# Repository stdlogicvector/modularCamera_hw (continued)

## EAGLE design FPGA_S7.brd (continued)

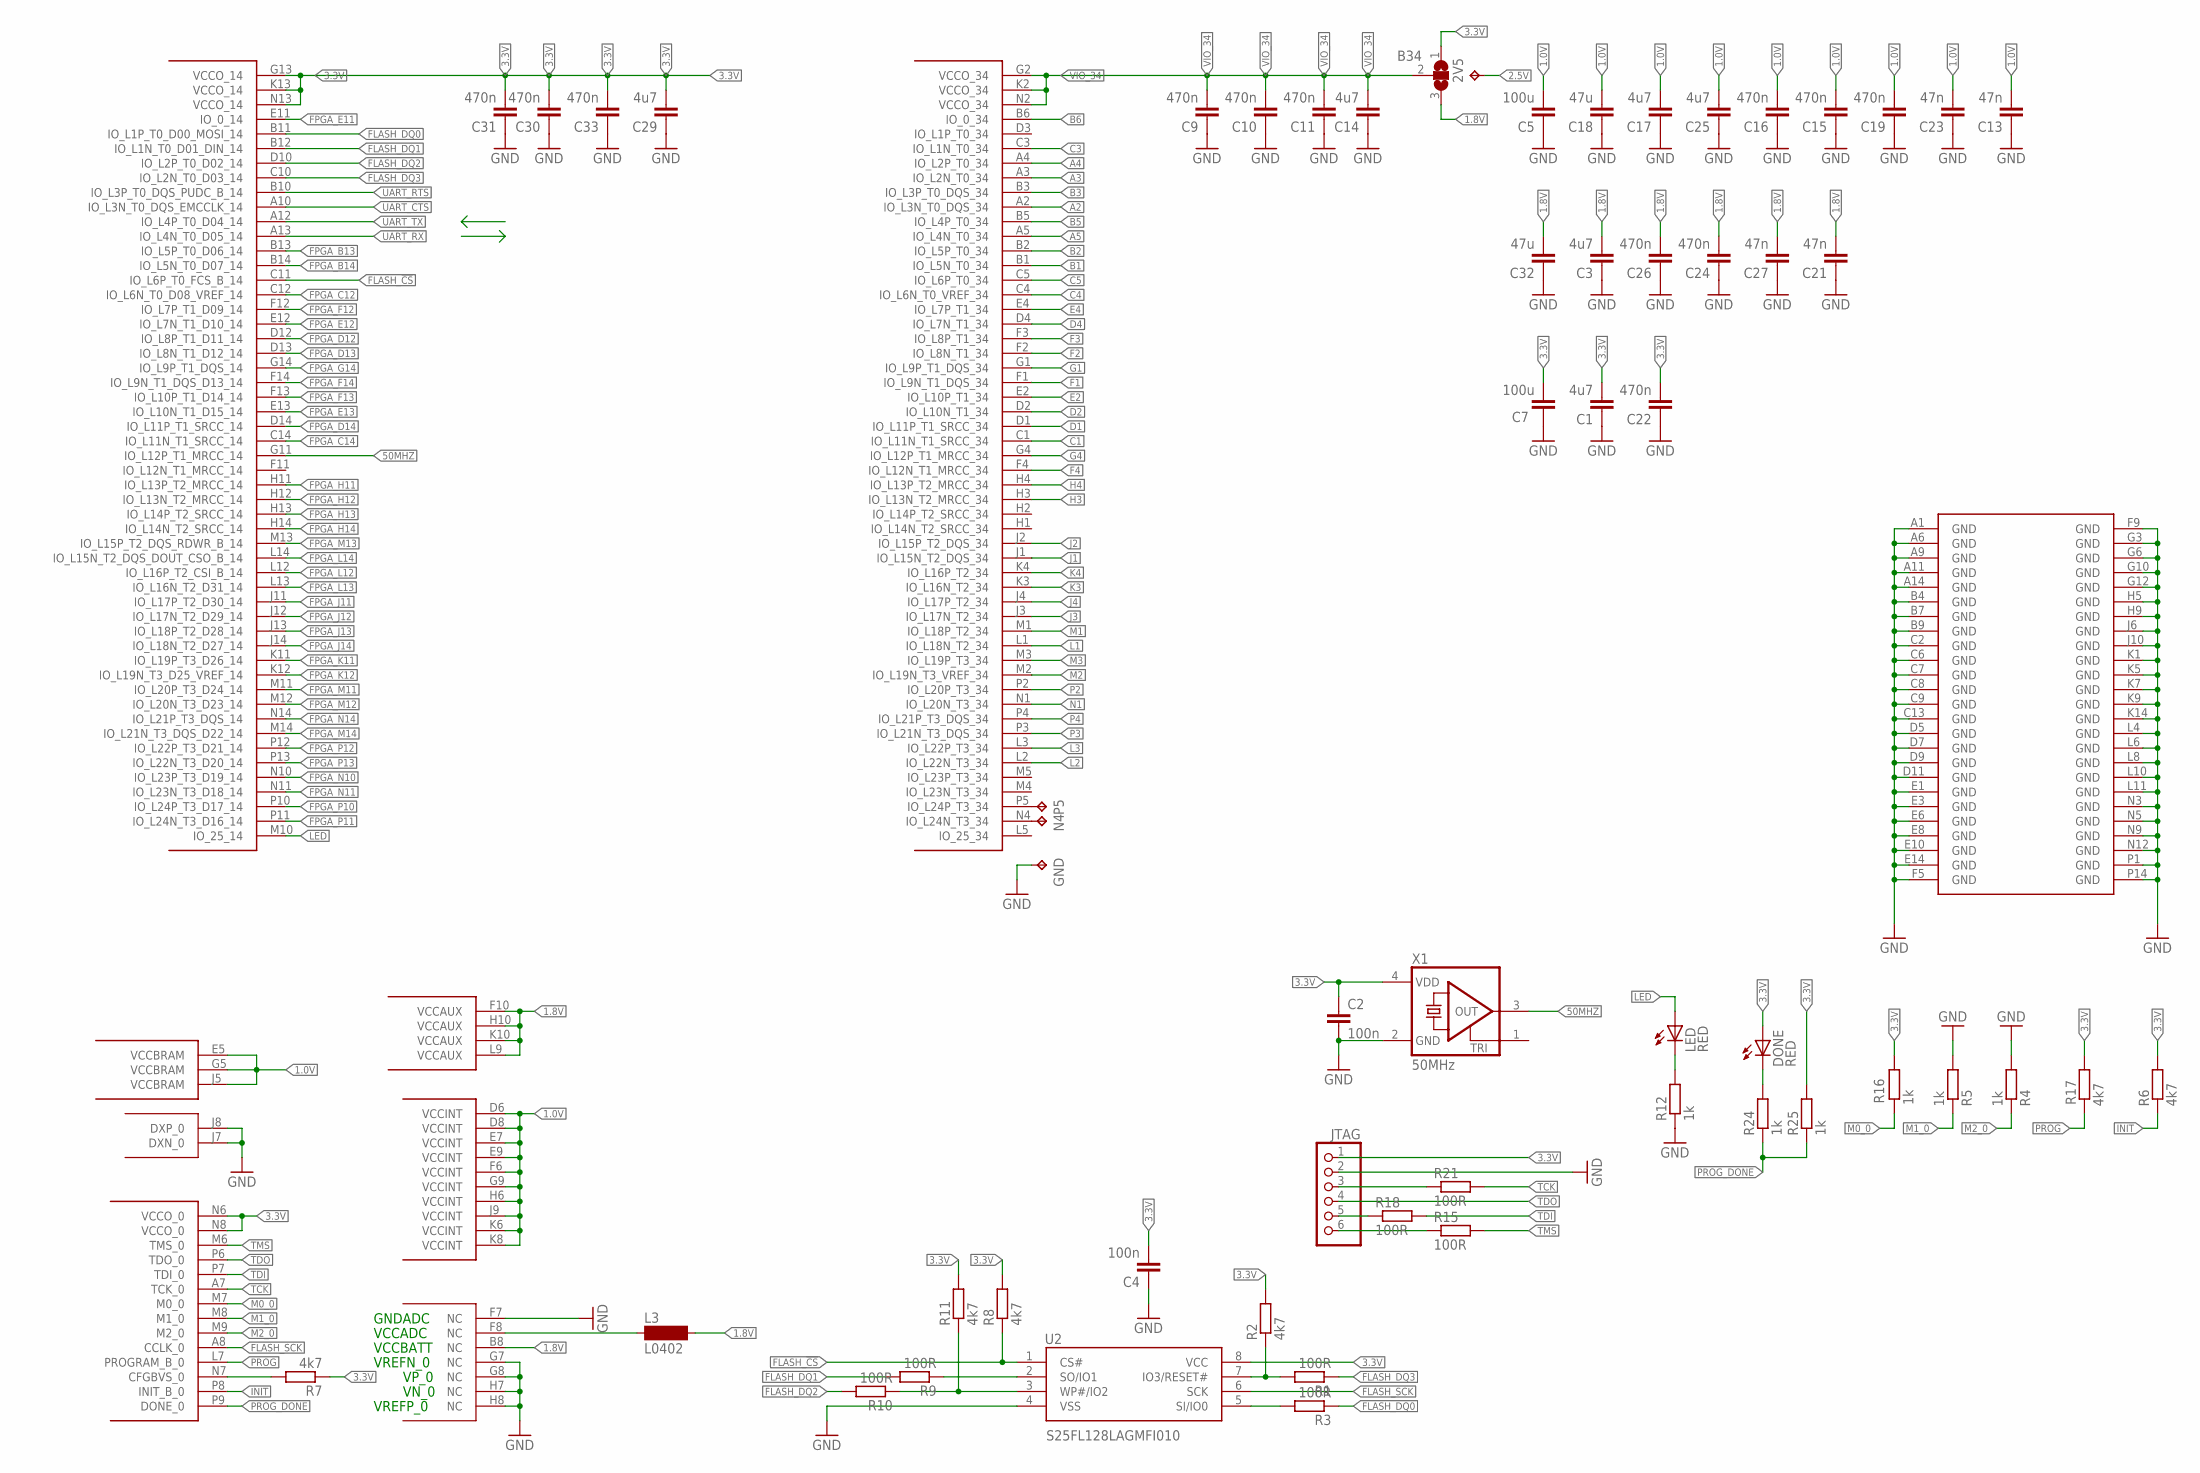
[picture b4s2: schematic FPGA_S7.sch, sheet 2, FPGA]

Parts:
2V5: TPTP12SQ; TP12SQ
B34: SJ2W; SJ_2
C1, C3, C14, C17, C25, C29: 4u7; C0603; LCSC C19666
C2, C4: 100n; C0402; LCSC C1525
C5, C7: 100u; C1206; DIGIKEY 490-GRM31CD80J107MEA8LCT-ND
C9, C10, C11, C15, C16, C19, C22, C24, C26, C30, C31, C33: 470n; C0402; LCSC C162159
C13, C21, C23, C27: 47n; C0402; LCSC C327054
C18, C32: 47u; C0805; LCSC C77072
DONE: RED; CHIP-LED0603; LCSC C7493803
GND: TPTP15R; TP15R
JTAG: PINHD-1X6_2.00; 1X06M
L3: L0402; C0402; LCSC C88970
LED: RED; CHIP-LED0603; LCSC C7493803
N4: TPTP15R; TP15R
P5: TPTP15R; TP15R
R1, R3, R9, R10, R15, R18, R21: 100R; R0402; LCSC C25076
R2, R6, R7, R8, R11, R17: 4k7; R0402; LCSC C25900
R4: 1k; R0402; LCSC C106235
R5, R12, R16, R24, R25: 1k; R0402; LCSC C11702
U1: XC7S15-2FTGB196I; BGA196C100P14X14_1500X1500X155; DIGIKEY 122-2233-ND
U2: S25FL128LAGMFI010; SOIC127P800X216-8N; MPN S25FL128LAGMFI010; DIGIKEY 448-S25FL128LAGMFI010-ND
X1: 50MHz; ASE; MPN_ ASE-50.000MHZ-E-T; FARNELL 2467898

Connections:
1.0V: C5.1, C13.2, C15.2, C16.2, C17.2, C18.1, C19.2, C23.2, C25.2, U1.D6 (VCCINT), U1.D8 (VCCINT), U1.E5 (VCCBRAM), U1.E7 (VCCINT), U1.E9 (VCCINT), U1.F6 (VCCINT), U1.G5 (VCCBRAM), U1.G9 (VCCINT), U1.H6 (VCCINT), U1.J5 (VCCBRAM), U1.J9 (VCCINT), U1.K6 (VCCINT), U1.K8 (VCCINT); also elsewhere on the board
1.8V: B34.3, C3.2, C21.2, C24.2, C26.2, C27.2, C32.2, L3.2, U1.B8 (NC), U1.F10 (VCCAUX), U1.H10 (VCCAUX), U1.K10 (VCCAUX), U1.L9 (VCCAUX); also elsewhere on the board
2.5V: 2V5.TP; also elsewhere on the board
3.3V: B34.1, C1.2, C2.1, C4.2, C7.1, C22.2, C29.2, C30.2, C31.2, C33.2, DONE.A, JTAG.1, R2.2, R6.2, R7.1, R8.2, R11.2, R16.1, R17.1, R25.2, U1.G13 (VCCO_14), U1.K13 (VCCO_14), U1.N6 (VCCO_0), U1.N8 (VCCO_0), U1.N13 (VCCO_14), U2.8 (VCC), X1.4 (VDD); also elsewhere on the board
50MHZ: U1.G11 (IO_L12P_T1_MRCC_14), X1.3 (OUT)
A2: U1.A2 (IO_L3N_T0_DQS_34); also elsewhere on the board
A3: U1.A3 (IO_L2N_T0_34); also elsewhere on the board
A4: U1.A4 (IO_L2P_T0_34); also elsewhere on the board
A5: U1.A5 (IO_L4N_T0_34); also elsewhere on the board
B1: U1.B1 (IO_L5N_T0_34); also elsewhere on the board
B2: U1.B2 (IO_L5P_T0_34); also elsewhere on the board
B3: U1.B3 (IO_L3P_T0_DQS_34); also elsewhere on the board
B5: U1.B5 (IO_L4P_T0_34); also elsewhere on the board
B6: U1.B6 (IO_0_34); also elsewhere on the board
C1: U1.C1 (IO_L11N_T1_SRCC_34); also elsewhere on the board
C3: U1.C3 (IO_L1N_T0_34); also elsewhere on the board
C4: U1.C4 (IO_L6N_T0_VREF_34); also elsewhere on the board
C5: U1.C5 (IO_L6P_T0_34); also elsewhere on the board
D1: U1.D1 (IO_L11P_T1_SRCC_34); also elsewhere on the board
D2: U1.D2 (IO_L10N_T1_34); also elsewhere on the board
D4: U1.D4 (IO_L7N_T1_34); also elsewhere on the board
E2: U1.E2 (IO_L10P_T1_34); also elsewhere on the board
E4: U1.E4 (IO_L7P_T1_34); also elsewhere on the board
F1: U1.F1 (IO_L9N_T1_DQS_34); also elsewhere on the board
F2: U1.F2 (IO_L8N_T1_34); also elsewhere on the board
F3: U1.F3 (IO_L8P_T1_34); also elsewhere on the board
F4: U1.F4 (IO_L12N_T1_MRCC_34); also elsewhere on the board
FLASH_!CS: R8.1, U1.C11 (IO_L6P_T0_FCS_B_14), U2.1 (CS#)
FLASH_DQ0: R3.1, U1.B11 (IO_L1P_T0_D00_MOSI_14)
FLASH_DQ1: R9.2, U1.B12 (IO_L1N_T0_D01_DIN_14)
FLASH_DQ2: R10.2, U1.D10 (IO_L2P_T0_D02_14)
FLASH_DQ3: R1.1, U1.C10 (IO_L2N_T0_D03_14)
FLASH_SCK: U1.A8 (CCLK_0), U2.6 (SCK)
FPGA_B13: U1.B13 (IO_L5P_T0_D06_14); also elsewhere on the board
FPGA_B14: U1.B14 (IO_L5N_T0_D07_14); also elsewhere on the board
FPGA_C12: U1.C12 (IO_L6N_T0_D08_VREF_14); also elsewhere on the board
FPGA_C14: U1.C14 (IO_L11N_T1_SRCC_14); also elsewhere on the board
FPGA_D12: U1.D12 (IO_L8P_T1_D11_14); also elsewhere on the board
FPGA_D13: U1.D13 (IO_L8N_T1_D12_14); also elsewhere on the board
FPGA_D14: U1.D14 (IO_L11P_T1_SRCC_14); also elsewhere on the board
FPGA_E11: U1.E11 (IO_0_14); also elsewhere on the board
FPGA_E12: U1.E12 (IO_L7N_T1_D10_14); also elsewhere on the board
FPGA_E13: U1.E13 (IO_L10N_T1_D15_14); also elsewhere on the board
FPGA_F12: U1.F12 (IO_L7P_T1_D09_14); also elsewhere on the board
FPGA_F13: U1.F13 (IO_L10P_T1_D14_14); also elsewhere on the board
FPGA_F14: U1.F14 (IO_L9N_T1_DQS_D13_14); also elsewhere on the board
FPGA_G14: U1.G14 (IO_L9P_T1_DQS_14); also elsewhere on the board
FPGA_H11: U1.H11 (IO_L13P_T2_MRCC_14); also elsewhere on the board
FPGA_H12: U1.H12 (IO_L13N_T2_MRCC_14); also elsewhere on the board
FPGA_H13: U1.H13 (IO_L14P_T2_SRCC_14); also elsewhere on the board
FPGA_H14: U1.H14 (IO_L14N_T2_SRCC_14); also elsewhere on the board
FPGA_J11: U1.J11 (IO_L17P_T2_D30_14); also elsewhere on the board
FPGA_J12: U1.J12 (IO_L17N_T2_D29_14); also elsewhere on the board
FPGA_J13: U1.J13 (IO_L18P_T2_D28_14); also elsewhere on the board
FPGA_J14: U1.J14 (IO_L18N_T2_D27_14); also elsewhere on the board
FPGA_K11: U1.K11 (IO_L19P_T3_D26_14); also elsewhere on the board
FPGA_K12: U1.K12 (IO_L19N_T3_D25_VREF_14); also elsewhere on the board
FPGA_L12: U1.L12 (IO_L16P_T2_CSI_B_14); also elsewhere on the board
FPGA_L13: U1.L13 (IO_L16N_T2_D31_14); also elsewhere on the board
FPGA_L14: U1.L14 (IO_L15N_T2_DQS_DOUT_CSO_B_14); also elsewhere on the board
FPGA_M11: U1.M11 (IO_L20P_T3_D24_14); also elsewhere on the board
FPGA_M12: U1.M12 (IO_L20N_T3_D23_14); also elsewhere on the board
FPGA_M13: U1.M13 (IO_L15P_T2_DQS_RDWR_B_14); also elsewhere on the board
FPGA_M14: U1.M14 (IO_L21N_T3_DQS_D22_14); also elsewhere on the board
FPGA_N10: U1.N10 (IO_L23P_T3_D19_14); also elsewhere on the board
FPGA_N11: U1.N11 (IO_L23N_T3_D18_14); also elsewhere on the board
FPGA_N14: U1.N14 (IO_L21P_T3_DQS_14); also elsewhere on the board
FPGA_P10: U1.P10 (IO_L24P_T3_D17_14); also elsewhere on the board
FPGA_P11: U1.P11 (IO_L24N_T3_D16_14); also elsewhere on the board
FPGA_P12: U1.P12 (IO_L22P_T3_D21_14); also elsewhere on the board
FPGA_P13: U1.P13 (IO_L22N_T3_D20_14); also elsewhere on the board
G1: U1.G1 (IO_L9P_T1_DQS_34); also elsewhere on the board
G4: U1.G4 (IO_L12P_T1_MRCC_34); also elsewhere on the board
GND: C1.1, C2.2, C3.1, C4.1, C5.2, C7.2, C9.1, C10.1, C11.1, C13.1, C14.1, C15.1, C16.1, C17.1, C18.2, C19.1, C21.1, C22.1, C23.1, C24.1, C25.1, C26.1, C27.1, C29.1, C30.1, C31.1, C32.1, C33.1, GND.TP, JTAG.2, R4.2, R5.2, R12.1, U1.A1 (GND), U1.A6 (GND), U1.A9 (GND), U1.A11 (GND), U1.A14 (GND), U1.B4 (GND), U1.B7 (GND), U1.B9 (GND), U1.C2 (GND), U1.C6 (GND), U1.C7 (GND), U1.C8 (GND), U1.C9 (GND), U1.C13 (GND), U1.D5 (GND), U1.D7 (GND), U1.D9 (GND), U1.D11 (GND), U1.E1 (GND), U1.E3 (GND), U1.E6 (GND), U1.E8 (GND), U1.E10 (GND), U1.E14 (GND), U1.F5 (GND), U1.F7 (NC), U1.F9 (GND), U1.G3 (GND), U1.G6 (GND), U1.G7 (NC), U1.G8 (NC), U1.G10 (GND), U1.G12 (GND), U1.H5 (GND), U1.H7 (NC), U1.H8 (NC), U1.H9 (GND), U1.J6 (GND), U1.J7 (DXN_0), U1.J8 (DXP_0), U1.J10 (GND), U1.K1 (GND), U1.K5 (GND), U1.K7 (GND), U1.K9 (GND), U1.K14 (GND), U1.L4 (GND), U1.L6 (GND), U1.L8 (GND), U1.L10 (GND), U1.L11 (GND), U1.N3 (GND), U1.N5 (GND), U1.N9 (GND), U1.N12 (GND), U1.P1 (GND), U1.P14 (GND), U2.4 (VSS), X1.2 (GND); also elsewhere on the board
H3: U1.H3 (IO_L13N_T2_MRCC_34); also elsewhere on the board
H4: U1.H4 (IO_L13P_T2_MRCC_34); also elsewhere on the board
INIT: R6.1, U1.P8 (INIT_B_0)
J1: U1.J1 (IO_L15N_T2_DQS_34); also elsewhere on the board
J2: U1.J2 (IO_L15P_T2_DQS_34); also elsewhere on the board
J3: U1.J3 (IO_L17N_T2_34); also elsewhere on the board
J4: U1.J4 (IO_L17P_T2_34); also elsewhere on the board
K3: U1.K3 (IO_L16N_T2_34); also elsewhere on the board
K4: U1.K4 (IO_L16P_T2_34); also elsewhere on the board
L1: U1.L1 (IO_L18N_T2_34); also elsewhere on the board
L2: U1.L2 (IO_L22N_T3_34); also elsewhere on the board
L3: U1.L3 (IO_L22P_T3_34); also elsewhere on the board
LED: LED.A, U1.M10 (IO_25_14)
M0_0: R16.2, U1.M7 (M0_0)
M1: U1.M1 (IO_L18P_T2_34); also elsewhere on the board
M1_0: R5.1, U1.M8 (M1_0)
M2: U1.M2 (IO_L19N_T3_VREF_34); also elsewhere on the board
M2_0: R4.1, U1.M9 (M2_0)
M3: U1.M3 (IO_L19P_T3_34); also elsewhere on the board
N1: U1.N1 (IO_L20N_T3_34); also elsewhere on the board
unnamed: L3.1, U1.F8 (NC)
unnamed: LED.C, R12.2
unnamed: R1.2, R2.1, U2.7 (IO3/RESET#)
unnamed: R7.2, U1.N7 (CFGBVS_0)
unnamed: R3.2, U2.5 (SI/IO0)
unnamed: R9.1, U2.2 (SO/IO1)
unnamed: R10.1, R11.1, U2.3 (WP#/IO2)
unnamed: P5.TP, U1.P5 (IO_L24P_T3_34)
unnamed: N4.TP, U1.N4 (IO_L24N_T3_34)
unnamed: DONE.C, R24.2
unnamed: JTAG.5, R18.1
unnamed: JTAG.3, R21.1
unnamed: JTAG.6, R15.1
P2: U1.P2 (IO_L20P_T3_34); also elsewhere on the board
P3: U1.P3 (IO_L21N_T3_DQS_34); also elsewhere on the board
P4: U1.P4 (IO_L21P_T3_DQS_34); also elsewhere on the board
PROG: R17.2, U1.L7 (PROGRAM_B_0)
PROG_DONE: R24.1, R25.1, U1.P9 (DONE_0)
TCK: R21.2, U1.A7 (TCK_0)
TDI: R18.2, U1.P7 (TDI_0)
TDO: JTAG.4, U1.P6 (TDO_0)
TMS: R15.2, U1.M6 (TMS_0)
UART_CTS: U1.A10 (IO_L3N_T0_DQS_EMCCLK_14); also elsewhere on the board
UART_RTS: U1.B10 (IO_L3P_T0_DQS_PUDC_B_14); also elsewhere on the board
UART_RX: U1.A13 (IO_L4N_T0_D05_14); also elsewhere on the board
UART_TX: U1.A12 (IO_L4P_T0_D04_14); also elsewhere on the board
VIO_34: B34.2, C9.2, C10.2, C11.2, C14.2, U1.G2 (VCCO_34), U1.K2 (VCCO_34), U1.N2 (VCCO_34)

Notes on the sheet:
GNDADC
VCCADC
VCCBATT
VP_0
VN_0
VREFP_0
VREFN_0

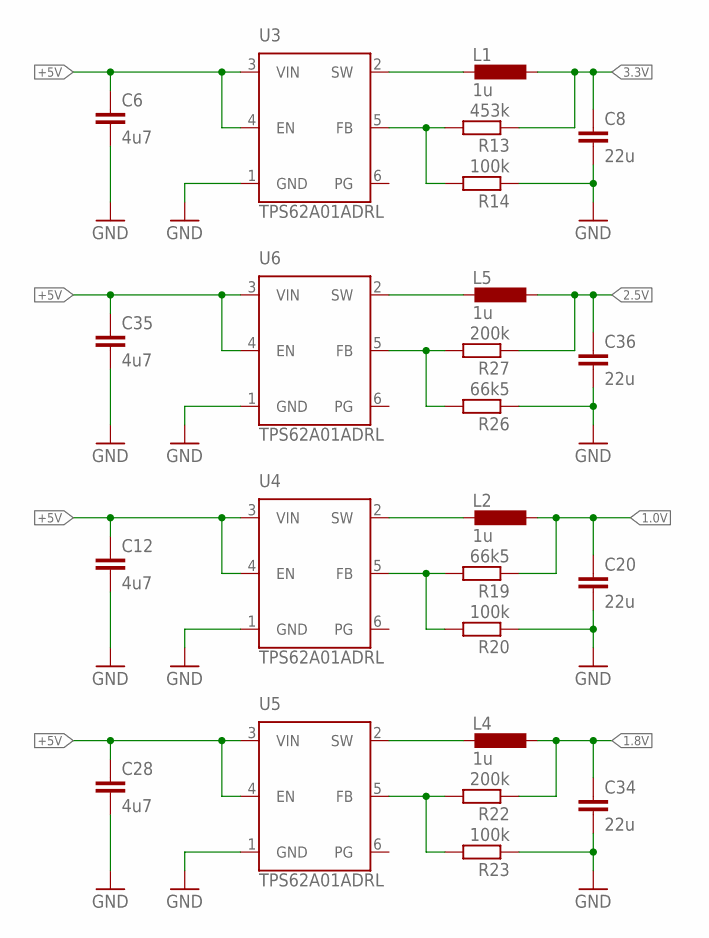
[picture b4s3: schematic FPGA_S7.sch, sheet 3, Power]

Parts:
C6, C12, C28, C35: 4u7; C0603; LCSC C19666
C8, C20, C34, C36: 22u; C0603; LCSC C109448
L1, L2, L4, L5: 1u; L1008; MPN LQM2HPN1R0MG0L; DIGIKEY 490-5112-1-ND
R13: 453k; R0402; LCSC C137978
R14: 100k; R0402; DIGIKEY RMCF0402FT100KCT-ND
R19: 66k5; R0402; DIGIKEY RMCF0402FT66K5CT-ND
R20, R23: 100k; R0402; LCSC C60491
R22: 200k; R0402; LCSC C114763
R26: 66k5; R0402; DIGIKEY RMCF0402FT100KCT-ND
R27: 200k; R0402; LCSC C137978
U3, U4, U5, U6: TPS62A01ADRL; SOTFL50P160X60-6N; DIGIKEY 296-TPS62A01ADRLRCT-ND

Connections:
1.0V: C20.1, L2.1, R19.1; also elsewhere on the board
1.8V: C34.1, L4.1, R22.1; also elsewhere on the board
2.5V: C36.1, L5.1, R27.1; also elsewhere on the board
3.3V: C8.1, L1.1, R13.1; also elsewhere on the board
+5V: C6.1, C12.1, C28.1, C35.1, U3.3 (VIN), U3.4 (EN), U4.3 (VIN), U4.4 (EN), U5.3 (VIN), U5.4 (EN), U6.3 (VIN), U6.4 (EN); also elsewhere on the board
GND: C6.2, C8.2, C12.2, C20.2, C28.2, C34.2, C35.2, C36.2, R14.1, R20.1, R23.1, R26.1, U3.1 (GND), U4.1 (GND), U5.1 (GND), U6.1 (GND); also elsewhere on the board
unnamed: L2.2, U4.2 (SW)
unnamed: L5.2, U6.2 (SW)
unnamed: R26.2, R27.2, U6.5 (FB)
unnamed: R19.2, R20.2, U4.5 (FB)
unnamed: R13.2, R14.2, U3.5 (FB)
unnamed: L4.2, U5.2 (SW)
unnamed: R22.2, R23.2, U5.5 (FB)
unnamed: L1.2, U3.2 (SW)

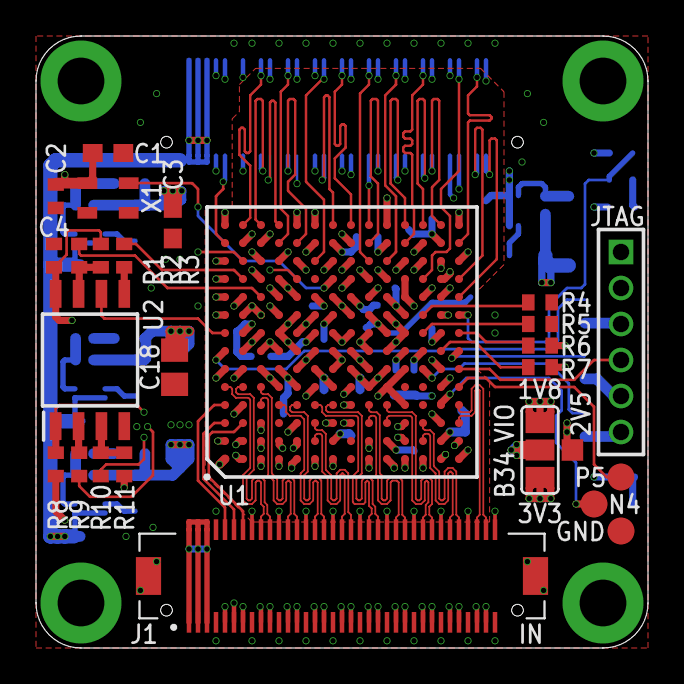
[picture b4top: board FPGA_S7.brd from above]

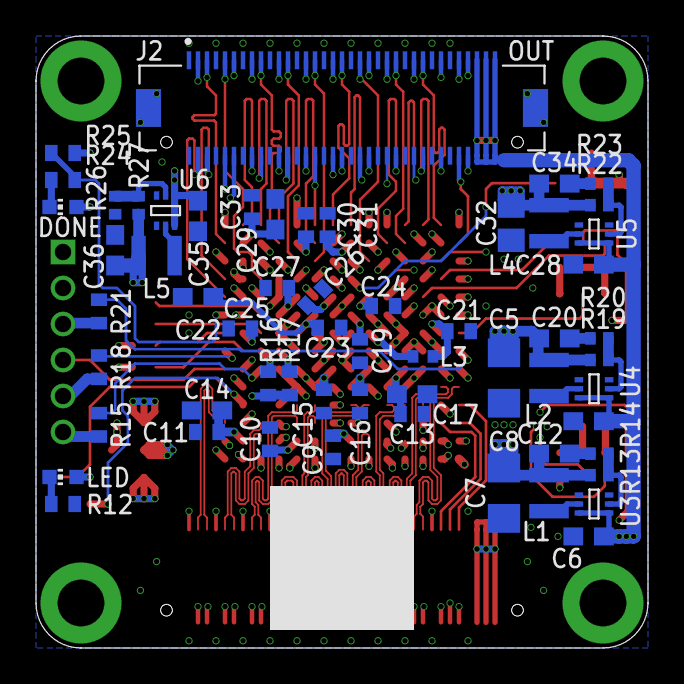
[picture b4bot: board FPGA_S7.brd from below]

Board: 6 copper layers, 34.0 x 34.0 mm, 85 parts (59 on the bottom side), 130 nets.

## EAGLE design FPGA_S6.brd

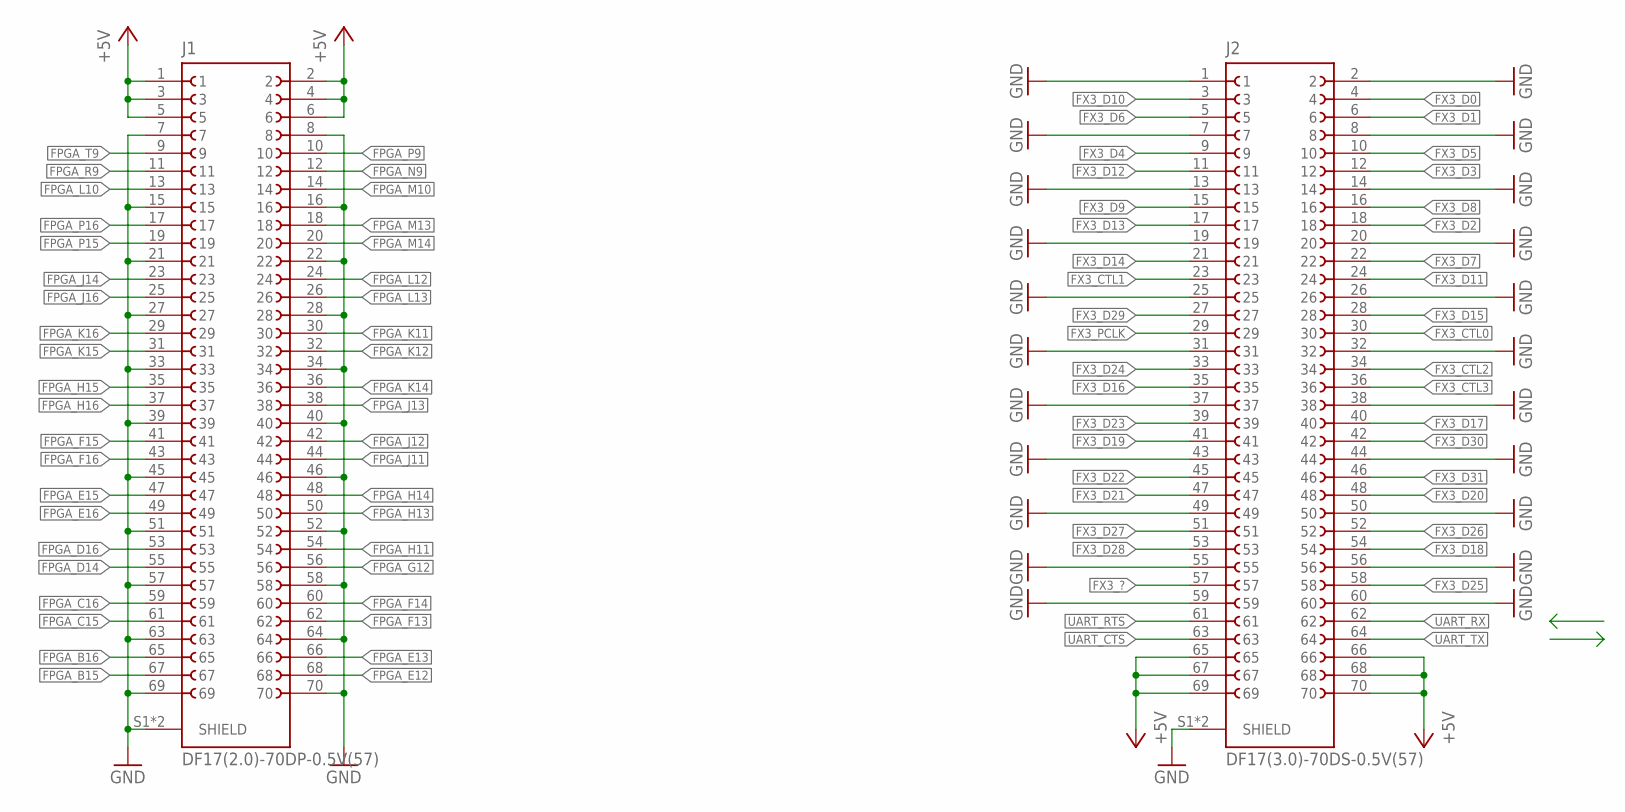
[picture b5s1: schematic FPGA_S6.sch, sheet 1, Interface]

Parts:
J1: DF17(2.0)-70DP-0.5V(57); DIGIKEY H11133CT-ND
J2: DF17(3.0)-70DS-0.5V(57); DIGIKEY H11112CT-ND

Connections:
+5V: J1.1, J1.2, J1.3, J1.4, J1.5, J1.6, J2.65, J2.66, J2.67, J2.68, J2.69, J2.70; also elsewhere on the board
FPGA_B15: J1.67; also elsewhere on the board
FPGA_B16: J1.65; also elsewhere on the board
FPGA_C15: J1.61; also elsewhere on the board
FPGA_C16: J1.59; also elsewhere on the board
FPGA_D14: J1.55; also elsewhere on the board
FPGA_D16: J1.53; also elsewhere on the board
FPGA_E12: J1.68; also elsewhere on the board
FPGA_E13: J1.66; also elsewhere on the board
FPGA_E15: J1.47; also elsewhere on the board
FPGA_E16: J1.49; also elsewhere on the board
FPGA_F13: J1.62; also elsewhere on the board
FPGA_F14: J1.60; also elsewhere on the board
FPGA_F15: J1.41; also elsewhere on the board
FPGA_F16: J1.43; also elsewhere on the board
FPGA_G12: J1.56; also elsewhere on the board
FPGA_H11: J1.54; also elsewhere on the board
FPGA_H13: J1.50; also elsewhere on the board
FPGA_H14: J1.48; also elsewhere on the board
FPGA_H15: J1.35; also elsewhere on the board
FPGA_H16: J1.37; also elsewhere on the board
FPGA_J11: J1.44; also elsewhere on the board
FPGA_J12: J1.42; also elsewhere on the board
FPGA_J13: J1.38; also elsewhere on the board
FPGA_J14: J1.23; also elsewhere on the board
FPGA_J16: J1.25; also elsewhere on the board
FPGA_K11: J1.30; also elsewhere on the board
FPGA_K12: J1.32; also elsewhere on the board
FPGA_K14: J1.36; also elsewhere on the board
FPGA_K15: J1.31; also elsewhere on the board
FPGA_K16: J1.29; also elsewhere on the board
FPGA_L10: J1.13; also elsewhere on the board
FPGA_L12: J1.24; also elsewhere on the board
FPGA_L13: J1.26; also elsewhere on the board
FPGA_M10: J1.14; also elsewhere on the board
FPGA_M13: J1.18; also elsewhere on the board
FPGA_M14: J1.20; also elsewhere on the board
FPGA_N9: J1.12; also elsewhere on the board
FPGA_P9: J1.10; also elsewhere on the board
FPGA_P15: J1.19; also elsewhere on the board
FPGA_P16: J1.17; also elsewhere on the board
FPGA_R9: J1.11; also elsewhere on the board
FPGA_T9: J1.9; also elsewhere on the board
FX3_?: J2.57; also elsewhere on the board
FX3_CTL0: J2.30; also elsewhere on the board
FX3_CTL1: J2.23; also elsewhere on the board
FX3_CTL2: J2.34; also elsewhere on the board
FX3_CTL3: J2.36; also elsewhere on the board
FX3_D0: J2.4; also elsewhere on the board
FX3_D1: J2.6; also elsewhere on the board
FX3_D2: J2.18; also elsewhere on the board
FX3_D3: J2.12; also elsewhere on the board
FX3_D4: J2.9; also elsewhere on the board
FX3_D5: J2.10; also elsewhere on the board
FX3_D6: J2.5; also elsewhere on the board
FX3_D7: J2.22; also elsewhere on the board
FX3_D8: J2.16; also elsewhere on the board
FX3_D9: J2.15; also elsewhere on the board
FX3_D10: J2.3; also elsewhere on the board
FX3_D11: J2.24; also elsewhere on the board
FX3_D12: J2.11; also elsewhere on the board
FX3_D13: J2.17; also elsewhere on the board
FX3_D14: J2.21; also elsewhere on the board
FX3_D15: J2.28; also elsewhere on the board
FX3_D16: J2.35; also elsewhere on the board
FX3_D17: J2.40; also elsewhere on the board
FX3_D18: J2.54; also elsewhere on the board
FX3_D19: J2.41; also elsewhere on the board
FX3_D20: J2.48; also elsewhere on the board
FX3_D21: J2.47; also elsewhere on the board
FX3_D22: J2.45; also elsewhere on the board
FX3_D23: J2.39; also elsewhere on the board
FX3_D24: J2.33; also elsewhere on the board
FX3_D25: J2.58; also elsewhere on the board
FX3_D26: J2.52; also elsewhere on the board
FX3_D27: J2.51; also elsewhere on the board
FX3_D28: J2.53; also elsewhere on the board
FX3_D29: J2.27; also elsewhere on the board
FX3_D30: J2.42; also elsewhere on the board
FX3_D31: J2.46; also elsewhere on the board
FX3_PCLK: J2.29; also elsewhere on the board
GND: J1.7, J1.8, J1.15, J1.16, J1.21, J1.22, J1.27, J1.28, J1.33, J1.34, J1.39, J1.40, J1.45, J1.46, J1.51, J1.52, J1.57, J1.58, J1.63, J1.64, J1.69, J1.70, J1.S1 (SHIELD), J1.S2 (SHIELD), J2.1, J2.2, J2.7, J2.8, J2.13, J2.14, J2.19, J2.20, J2.25, J2.26, J2.31, J2.32, J2.37, J2.38, J2.43, J2.44, J2.49, J2.50, J2.55, J2.56, J2.59, J2.60, J2.S1 (SHIELD), J2.S2 (SHIELD); also elsewhere on the board
UART_CTS: J2.63; also elsewhere on the board
UART_RTS: J2.61; also elsewhere on the board
UART_RX: J2.62; also elsewhere on the board
UART_TX: J2.64; also elsewhere on the board
